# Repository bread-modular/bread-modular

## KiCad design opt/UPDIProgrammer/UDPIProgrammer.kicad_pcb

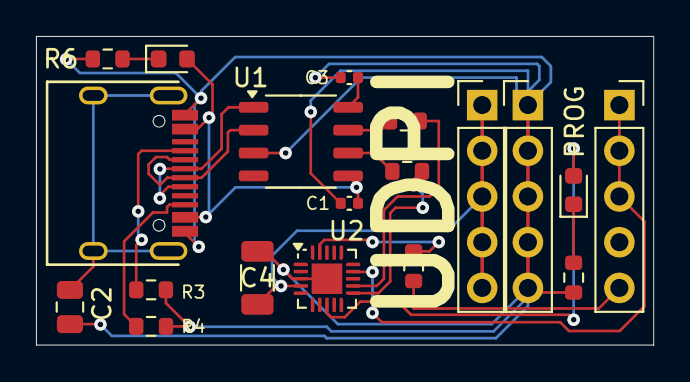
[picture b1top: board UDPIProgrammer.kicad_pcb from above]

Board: 2 copper layers, 34.3 x 17.1 mm, 19 parts (0 on the bottom side), 19 nets.

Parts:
C1, C3: 0.1uf; C_0402_1005Metric
C2: 10nf; C_0805_2012Metric
C4: 100uf; C_1206_3216Metric
D1, D2: LED; LED_0603_1608Metric
GND1: Conn_01x05_Pin; PinHeader_1x05_P2.54mm_Vertical
J2: USB_C_Receptacle_USB2.0_14P; HRO-TYPE-C-31-M-12
OUTPUT1: Conn_01x05_Socket; PinSocket_1x05_P2.54mm_Vertical
R1, R2, R6, R7: 1k; R_0603_1608Metric
R3, R4: 5.1k; R_0603_1608Metric
R5: 4.7k; R_0603_1608Metric
U1: CH340N; SOP-8_3.9x4.9mm_P1.27mm
U2: ATtiny1616-M; VQFN-20-1EP_3x3mm_P0.4mm_EP1.7x1.7mm
VSUPPLY1: Conn_01x05_Pin; PinHeader_1x05_P2.54mm_Vertical

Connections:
5V: C1.1, D1.2 (A), J2.A4 (VBUS), J2.A9 (VBUS), U1.5 (VCC)
+3.3V: C4.2, U2.4 (VCC), VSUPPLY1.1, VSUPPLY1.2, VSUPPLY1.3, VSUPPLY1.4, VSUPPLY1.5
D+: J2.A6 (D+), J2.B6 (D+), U1.1 (UD+)
D-: J2.A7 (D-), J2.B7 (D-), U1.2 (UD-)
GND: C1.2, C2.2, C3.1, C4.1, GND1.1, GND1.2, GND1.3, GND1.4, GND1.5, J2.A1 (GND), J2.A12 (GND), R3.2, R4.2, R6.2, R7.2, U1.3 (GND), U2.3 (GND), U2.21 (GND)
LED: D2.2 (A), U2.8 (PA7)
MCU_UDPI: OUTPUT1.5, R5.2
unnamed: D1.1 (K), R6.1
unnamed: D2.1 (K), R7.1
unnamed: J2.A5 (CC1), R3.1
unnamed: J2.B5 (CC2), R4.1
unnamed: C2.1, J2.S1 (SHIELD)
unnamed: R2.1, U1.7 (RXD)
unnamed: R1.1, U1.6 (TXD)
unnamed: C3.2, U1.8 (V3)
unnamed: R5.1, U2.19 (~RESET/PA0)
PROG: OUTPUT1.1, OUTPUT1.2, OUTPUT1.3, U2.14 (PB0)
SERIAL_RX: R2.2, U2.12 (PB2)
SERIAL_TX: R1.2, U2.11 (PB3)

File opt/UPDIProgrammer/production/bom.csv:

Designator,Footprint,Quantity,Value,LCSC Part #
"C1, C3",0402,2,0.1uf,
C2,0805,1,10nf,
C4,1206,1,100uf,
"D1, D2",0603,2,LED,
"GND1, VSUPPLY1",PinHeader_1x05_P2.54mm_Vertical,2,Conn_01x05_Pin,
J2,HRO-TYPE-C-31-M-12,1,USB_C_Receptacle_USB2.0_14P,
OUTPUT1,PinSocket_1x05_P2.54mm_Vertical,1,Conn_01x05_Socket,
"R1, R2, R6, R7",0603,4,1k,
"R3, R4",0603,2,5.1k,
R5,0603,1,4.7k,
U1,SOP-8_3.9x4.9mm_P1.27mm,1,CH340N,
U2,VQFN-20-1EP_3x3mm_P0.4mm_EP1.7x1.7mm,1,ATtiny1616-M,
